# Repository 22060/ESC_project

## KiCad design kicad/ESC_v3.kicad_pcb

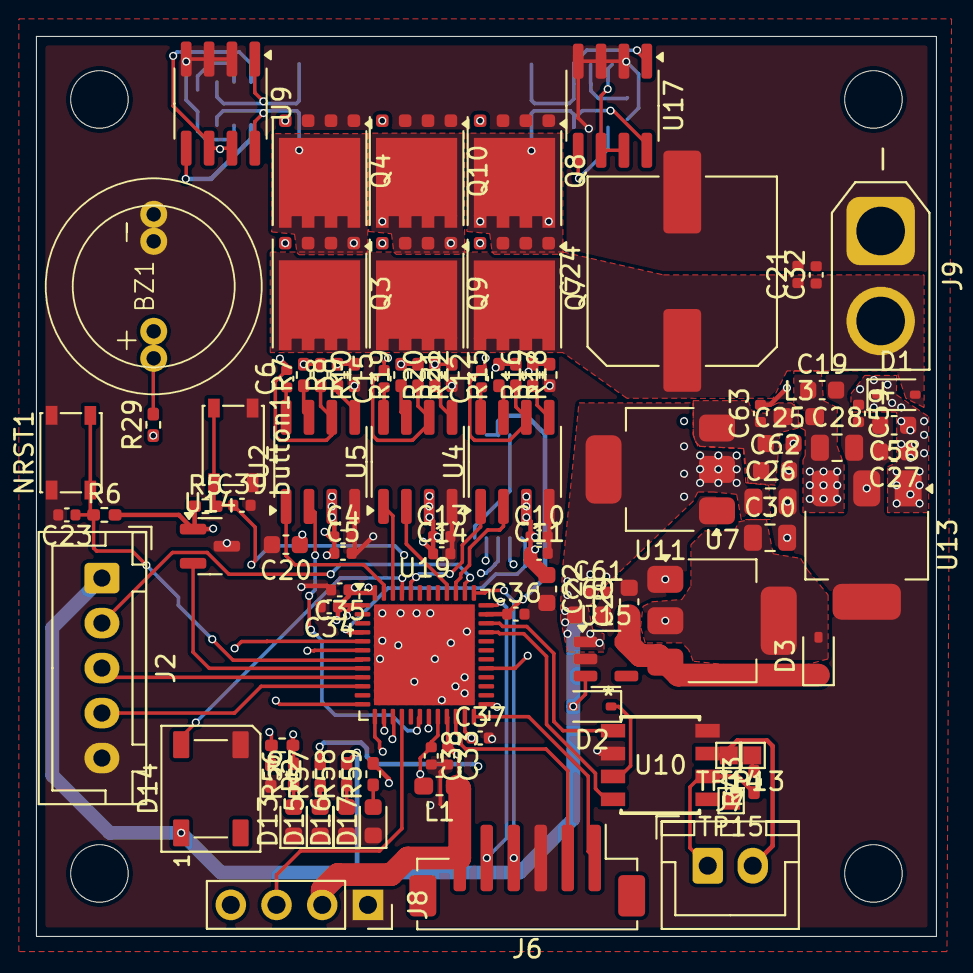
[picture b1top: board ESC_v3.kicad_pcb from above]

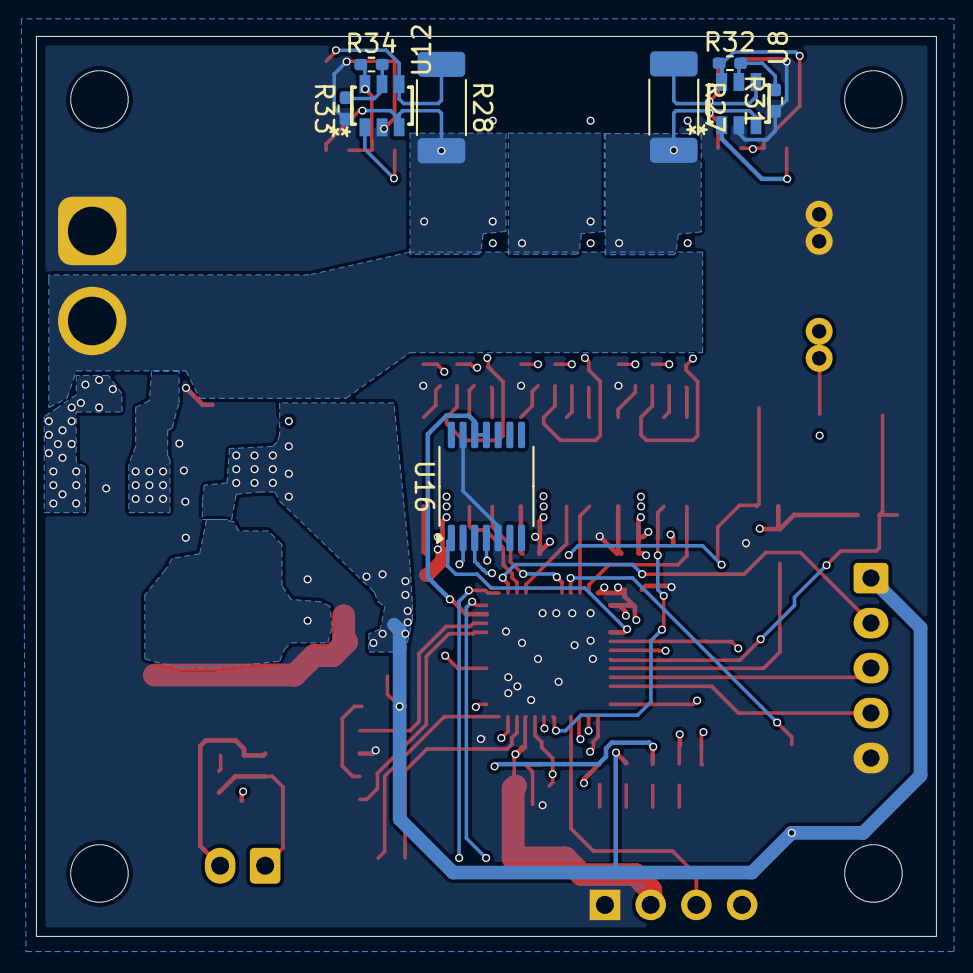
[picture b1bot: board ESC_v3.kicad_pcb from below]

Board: 6 copper layers, 50.0 x 50.0 mm, 109 parts (9 on the bottom side), 69 nets.

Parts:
BZ1: Buzzer; buzzer_unified
C4, C6, C10, C12, C13, C15, C23, C32, C38, C39, C59, C61, C63: 0.1u; C_0402_1005Metric
C5, C11, C14, C21, C33, C34, C35, C36, C37: 1u; C_0402_1005Metric
C19, C20, C22: 10u; C_0603_1608Metric
C24: 470u; C_Elec_10x10.2
C25, C29: 10uF; C_0603_1608Metric
C26, C28, C30: 22uF; C_0805_2012Metric
C27: 0.47uF; C_0603_1608Metric
C58, C60, C62: 100u; C_0603_1608Metric
D1, D2, D3: 1N5819WS; D_SOD-323
D13, D15, D16, D17: LED; LED_0603_1608Metric
D14: WS2812B; LED_WS2812B_PLCC4_5.0x5.0mm_P3.2mm
H1, H2, H3, H4: MountingHole; MountingHole_3.2mm_M3
J2: Conn_01x05_Pin; JST_XH_B5B-XH-A_1x05_P2.50mm_Vertical
J6: Conn_01x06_Pin; JST_ZH_B6B-ZR-SM4-TF_1x06-1MP_P1.50mm_Vertical
J7: Conn_01x02_Pin; JST_XH_B2B-XH-A_1x02_P2.50mm_Vertical
J8: Conn_01x04_Pin; PinSocket_1x04_P2.54mm_Vertical
J9: Conn_01x02_Pin; AMASS_XT30U-M_1x02_P5.0mm_Vertical
L1, L3: L; L_0603_1608Metric_Pad1.05x0.95mm_HandSolder
NRST1: SW_Push; SW_SPST_PTS810
Q3, Q4, Q7, Q8, Q9, Q10: RH6L040BGTB1; VSONP-8-1EP_5x6_P1.27mm
R1: 68k; R_0402_1005Metric_Pad0.72x0.64mm_HandSolder
R2, R5, R6, R9, R10, R17, R18, R21, R22, R57: 10k; R_0402_1005Metric_Pad0.72x0.64mm_HandSolder
R7, R8, R15, R16, R19, R20: 22; R_0402_1005Metric_Pad0.72x0.64mm_HandSolder
R27, R28: 2mΩ; R_2010_5025Metric_Pad1.40x2.65mm_HandSolder
R29: 100; R_0402_1005Metric_Pad0.72x0.64mm_HandSolder
R31, R32, R33, R34: 100k; R_0402_1005Metric_Pad0.72x0.64mm_HandSolder
R43: 120; R_0402_1005Metric_Pad0.72x0.64mm_HandSolder
R56: 22k; R_0402_1005Metric_Pad0.72x0.64mm_HandSolder
R58: 4.7k; R_0402_1005Metric_Pad0.72x0.64mm_HandSolder
R59: 2.2k; R_0402_1005Metric_Pad0.72x0.64mm_HandSolder
TP13, TP14, TP15: TestPoint; TestPoint_Pad_1.0x1.0mm
U2, U4, U5: L6387; SOIC-8_3.9x4.9mm_P1.27mm
U7: AMS1117-3.3; SOT-223-3_TabPin2
U8, U12: BD14210G; SSOP6
U9, U17: INA240A1D; SOIC-8_3.9x4.9mm_P1.27mm
U10: BD4104; SOP-J8
U11: AMS1117-5.0; SOT-223-3_TabPin2
U13: LM2937xMP; SOT-223-3_TabPin2
U14: MCP9700x-ETT; SOT-23
U15: MAX40200AUK; SOT-23-5
U16: AS5048A; TSSOP-14_4.4x5mm_P0.65mm
U19: STM32G431CBUx; QFN-48-1EP_7x7mm_P0.5mm_EP5.6x5.6mm
button1: SW_Push; SW_SPST_PTS810

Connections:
+3.3V: C30.1, C33.1, C34.1, C35.1, C36.1, C37.1, D3.2 (A), J6.6, J8.2, L1.1, R5.1, R6.2, R59.2, TP15.1, U7.2 (VO), U14.1 (V_{DD}), U16.11 (VDD5V), U16.12 (VDD3V), U19.1 (VBAT), U19.21 (VDDA), U19.23 (VDD), U19.35 (VDD), U19.48 (VDD)
+5V: C26.1, C60.1, C61.1, D2.2 (A), D14.1 (VDD), J2.1, R58.2, U11.2 (VO), U15.1 (VDD), U15.3 (EN)
+12V: C4.1, C5.1, C10.1, C11.1, C13.1, C14.1, C19.1, C20.1, C22.1, C28.1, L3.2, R57.2, U2.3 (VCC), U4.3 (VCC), U5.3 (VCC), U13.3 (VO)
/POWER/halfHbridge5/out1: C6.2, Q3.1 (S), Q4.3 (D), R10.2, R27.2, U2.6 (VS), U8.3 (VINP), U9.8 (+)
/POWER/halfHbridge7/out1: C12.2, Q7.1 (S), Q8.3 (D), R18.2, R28.2, U4.6 (VS), U12.3 (VINP), U17.8 (+)
/POWER/halfHbridge8/out1: C15.2, Q9.1 (S), Q10.3 (D), R22.2, U5.6 (VS)
ADC1_IN1: U14.2 (V_{OUT}), U19.8 (PA0)
ADC1_IN11: U12.1 (OUT), U17.5, U19.25 (PB12)
ADC2_IN10: R1.2, R2.1, U19.6 (PF1)
ADC2_IN12: U8.1 (OUT), U9.5, U19.19 (PB2)
CAN_H: J7.2, TP14.1, U10.7 (H)
CAN_L: J7.1, R43.1, U10.6 (L)
CAN_RX: U10.4 (RX), U19.33 (PA11)
CAN_TX: U10.1 (TX), U19.34 (PA12)
CLK: J6.4, U19.37 (PA14)
DAC1_OUT: R29.1, U19.12 (PA4)
DIO: J6.5, U19.36 (PA13)
GND: BZ1.2 (-), C4.2, C5.2, C10.2, C11.2, C13.2, C14.2, C19.2, C20.2, C21.2, C22.2, C23.2, C24.2, C25.2, C26.2, C27.2, C28.2, C29.2, C30.2, C32.2, C33.2, C34.2, C35.2, C36.2, C37.2, C38.2, C39.2, C58.2, C59.2, C60.2, C61.2, C62.2, C63.2, D13.1 (K), D14.3 (VSS), D15.1 (K), D16.1 (K), D17.1 (K), J2.5, J6.3, J8.1, J9.1, NRST1.1, Q4.1 (S), Q8.1 (S), Q10.1 (S), R2.2, R9.1, R17.1, R21.1, R31.1, R33.1, U2.4 (COM), U4.4 (COM), U5.4 (COM), U7.1 (GND), U8.2 (GND), U9.2 (GND), U9.3 (REF2), U9.4 (GND), U10.2 (GND), U10.8 (STB), U11.1 (GND), U12.2 (GND), U13.2 (GND), U14.3 (GND), U15.2 (GND), U16.5 (TEST), U16.13 (GND), U17.2 (GND), U17.3 (REF2), U17.4 (GND), U19.49 (VSS), button1.1
I2C_SCL: J8.3, U19.16 (PC4)
I2C_SDA: J8.4, U19.5 (PF0)
NRST: C23.1, NRST1.2, R6.1, U19.7 (PG10)
unnamed: BZ1.1 (+), R29.2
unnamed: C27.1, C58.1, C59.1, D1.1 (K), U13.1 (VI)
unnamed: D2.1 (K), U10.3 (VCC)
unnamed: C29.1, D3.1 (K), U7.3 (VI), U15.5 (OUT)
unnamed: D13.2 (A), R56.1
unnamed: D15.2 (A), R57.1
unnamed: D16.2 (A), R58.1
unnamed: D17.2 (A), R59.1
unnamed: Q3.2 (G), R7.2, R10.1
unnamed: Q4.2 (G), R8.2, R9.2
unnamed: Q7.2 (G), R15.2, R18.1
unnamed: Q8.2 (G), R16.2, R17.2
unnamed: Q9.2 (G), R19.2, R22.1
unnamed: Q10.2 (G), R20.2, R21.2
unnamed: R43.2, TP13.1
unnamed: R7.1, U2.7 (HO)
unnamed: R8.1, U2.5 (LO)
unnamed: C6.1, U2.8 (VB)
unnamed: R15.1, U4.7 (HO)
unnamed: R16.1, U4.5 (LO)
unnamed: C12.1, U4.8 (VB)
unnamed: R19.1, U5.7 (HO)
unnamed: R20.1, U5.5 (LO)
unnamed: C15.1, U5.8 (VB)
unnamed: R31.2, R32.2, U8.5 (REF)
unnamed: R27.1, U8.4 (VINM), U9.1 (-)
unnamed: C25.1, C62.1, C63.1, L3.1, U11.3 (VI)
unnamed: R33.2, R34.2, U12.5 (REF)
unnamed: R28.1, U12.4 (VINM), U17.1 (-)
RX: J6.1, U19.24 (PB11)
SPI1_MISO: U16.3 (MISO), U19.14 (PA6)
SPI1_MOSI: U16.4 (MOSI), U19.15 (PA7)
SPI1_SCK: U16.2 (CLK), U19.13 (PA5)
SS: U16.1 (~CSn), U19.4 (PC15)
TIM2_CH1: J2.2, U19.38 (PA15)
TIM2_CH2: J2.3, U19.9 (PA1)
TIM2_CH3: J2.4, U19.10 (PA2)
TIM4_CH2: D14.4 (DIN), U19.45 (PB7)
TIM8_CH1: U4.1 (HIN), U19.44 (PB6)
TIM8_CH1N: U4.2 (LIN), U19.39 (PC10)
TIM8_CH2: U5.1 (HIN), U19.46 (PB8)
TIM8_CH2N: U5.2 (LIN), U19.40 (PC11)
TIM8_CH3: U2.1 (HIN), U19.47 (PB9)
TIM8_CH3N: U2.2 (LIN), U19.18 (PB1)
TX: J6.2, U19.22 (PB10)
VCC: C21.1, C24.1, C32.1, D1.2 (A), J9.2, Q3.3 (D), Q7.3 (D), Q9.3 (D), R1.1, R56.2
VREF: C38.1, L1.2, R32.1, R34.1, U8.6 (VDD), U9.6 (V+), U9.7 (REF1), U12.6 (VDD), U17.6 (V+), U17.7 (REF1), U19.20 (VREF+)
button: C39.1, R5.2, U19.29 (PC6), button1.2

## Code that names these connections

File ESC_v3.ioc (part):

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Mcu.Name=STM32G431C(6-8-B)Ux
Mcu.Package=UFQFPN48
Mcu.UserName=STM32G431CBUx
PA0.Mode=IN1-Single-Ended
PA0.Signal=ADC1_IN1
PA1.Signal=S_TIM2_CH2
PA10.Signal=S_TIM1_CH3
PA11.Mode=FDCAN_Activate
PA11.Signal=FDCAN1_RX
PA12.Mode=FDCAN_Activate
PA12.Signal=FDCAN1_TX
PA13.Mode=Serial_Wire
PA13.Signal=SYS_JTMS-SWDIO
PA14.Mode=Serial_Wire
PA14.Signal=SYS_JTCK-SWCLK
PA15.Signal=S_TIM2_CH1
PA2.Signal=SharedStack_PA2
PA2.Stacked=true
PA3.Mode=PGA_Internally_Connected
PA3.Signal=OPAMP1_VINP
PA4.Signal=COMP_DAC11_group
PA5.Mode=Full_Duplex_Master
PA5.Signal=SPI1_SCK
PA6.Mode=Full_Duplex_Master
PA6.Signal=SPI1_MISO
PA7.Mode=Full_Duplex_Master
PA7.Signal=SPI1_MOSI
PA8.Signal=S_TIM1_CH1
PA9.Signal=S_TIM1_CH2
PB0.Mode=PGA_Internally_Connected
PB0.Signal=OPAMP2_VINP
PB1.Mode=PWM Generation3 CH3 CH3N
PB1.Signal=TIM8_CH3N
PB10.Mode=Asynchronous
PB10.Signal=USART3_TX
PB11.Mode=Asynchronous
PB11.Signal=USART3_RX
PB12.Mode=IN11-Single-Ended
PB12.Signal=ADC1_IN11
PB13.Mode=PGA_Internally_Connected
PB13.Signal=OPAMP3_VINP
PB14.Mode=PWM Generation2 CH2 CH2N
PB14.Signal=TIM1_CH2N
PB15.Mode=PWM Generation3 CH3 CH3N
PB15.Signal=TIM1_CH3N
PB2.Mode=IN12-Single-Ended
PB2.Signal=ADC2_IN12
PB3.Signal=SharedStack_PB3
PB3.Stacked=true
PB4.Signal=SharedStack_PB4
PB4.Stacked=true
PB5.Signal=S_TIM3_CH2
PB5.Stacked=true
PB6.Signal=S_TIM8_CH1
PB7.Signal=S_TIM4_CH2
PB8-BOOT0.Signal=S_TIM8_CH2
PB9.Signal=S_TIM8_CH3
PC10.Mode=PWM Generation1 CH1 CH1N
PC10.Signal=TIM8_CH1N
PC11.Mode=PWM Generation2 CH2 CH2N
PC11.Signal=TIM8_CH2N
PC13.Mode=PWM Generation1 CH1 CH1N
PC13.Signal=TIM1_CH1N
PC14-OSC32_IN.Signal=GPIO_Input
PC15-OSC32_OUT.Signal=GPIO_Output
PC4.Mode=I2C
PC4.Signal=I2C2_SCL
PC6.Signal=GPIO_Input
PF0-OSC_IN.Mode=I2C
PF0-OSC_IN.Signal=I2C2_SDA
PF1-OSC_OUT.Mode=IN10-Single-Ended
PF1-OSC_OUT.Signal=ADC2_IN10
RCC.HSE_VALUE=8000000
RCC.SYSCLKFreq_VALUE=100000000
RCC.SYSCLKSource=RCC_SYSCLKSOURCE_PLLCLK
board=custom

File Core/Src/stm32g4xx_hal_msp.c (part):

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    __HAL_RCC_GPIOA_CLK_ENABLE();
    __HAL_RCC_GPIOB_CLK_ENABLE();
    /**ADC1 GPIO Configuration
    PA0     ------> ADC1_IN1
    PB12     ------> ADC1_IN11
    */
    GPIO_InitStruct.Pin = GPIO_PIN_0;
    GPIO_InitStruct.Mode = GPIO_MODE_ANALOG;
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    __HAL_RCC_GPIOF_CLK_ENABLE();
    __HAL_RCC_GPIOB_CLK_ENABLE();
    /**ADC2 GPIO Configuration
    PF1-OSC_OUT     ------> ADC2_IN10
    PB2     ------> ADC2_IN12
    */
    GPIO_InitStruct.Pin = GPIO_PIN_1;
    GPIO_InitStruct.Mode = GPIO_MODE_ANALOG;
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    }

    /**ADC1 GPIO Configuration
    PA0     ------> ADC1_IN1
    PB12     ------> ADC1_IN11
    */
    HAL_GPIO_DeInit(GPIOA, GPIO_PIN_0);

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    }

    /**ADC2 GPIO Configuration
    PF1-OSC_OUT     ------> ADC2_IN10
    PB2     ------> ADC2_IN12
    */
    HAL_GPIO_DeInit(GPIOF, GPIO_PIN_1);

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
    __HAL_RCC_GPIOA_CLK_ENABLE();
    /**DAC1 GPIO Configuration
    PA4     ------> DAC1_OUT1
    */
    GPIO_InitStruct.Pin = GPIO_PIN_4;
    GPIO_InitStruct.Mode = GPIO_MODE_ANALOG;
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    __HAL_RCC_DAC1_CLK_DISABLE();

    /**DAC1 GPIO Configuration
    PA4     ------> DAC1_OUT1
    */
    HAL_GPIO_DeInit(GPIOA, GPIO_PIN_4);

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
    __HAL_RCC_GPIOA_CLK_ENABLE();
    /**FDCAN1 GPIO Configuration
    PA11     ------> FDCAN1_RX
    PA12     ------> FDCAN1_TX
    */
    GPIO_InitStruct.Pin = GPIO_PIN_11|GPIO_PIN_12;
    GPIO_InitStruct.Mode = GPIO_MODE_AF_PP;
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    __HAL_RCC_FDCAN_CLK_DISABLE();

    /**FDCAN1 GPIO Configuration
    PA11     ------> FDCAN1_RX
    PA12     ------> FDCAN1_TX
    */
    HAL_GPIO_DeInit(GPIOA, GPIO_PIN_11|GPIO_PIN_12);

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    __HAL_RCC_GPIOF_CLK_ENABLE();
    __HAL_RCC_GPIOC_CLK_ENABLE();
    /**I2C2 GPIO Configuration
    PF0-OSC_IN     ------> I2C2_SDA
    PC4     ------> I2C2_SCL
    */
    GPIO_InitStruct.Pin = GPIO_PIN_0;
    GPIO_InitStruct.Mode = GPIO_MODE_AF_OD;
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    __HAL_RCC_I2C2_CLK_DISABLE();

    /**I2C2 GPIO Configuration
    PF0-OSC_IN     ------> I2C2_SDA
    PC4     ------> I2C2_SCL
    */
    HAL_GPIO_DeInit(GPIOF, GPIO_PIN_0);

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
    __HAL_RCC_GPIOA_CLK_ENABLE();
    /**SPI1 GPIO Configuration
    PA5     ------> SPI1_SCK
    PA6     ------> SPI1_MISO
    PA7     ------> SPI1_MOSI
    */
    GPIO_InitStruct.Pin = GPIO_PIN_5|GPIO_PIN_6|GPIO_PIN_7;
    GPIO_InitStruct.Mode = GPIO_MODE_AF_PP;
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    __HAL_RCC_SPI1_CLK_DISABLE();

    /**SPI1 GPIO Configuration
    PA5     ------> SPI1_SCK
    PA6     ------> SPI1_MISO
    PA7     ------> SPI1_MOSI
    */
    HAL_GPIO_DeInit(GPIOA, GPIO_PIN_5|GPIO_PIN_6|GPIO_PIN_7);

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
    __HAL_RCC_GPIOA_CLK_ENABLE();
    /**TIM2 GPIO Configuration
    PA1     ------> TIM2_CH2
    PA15     ------> TIM2_CH1
    */
    GPIO_InitStruct.Pin = GPIO_PIN_1|GPIO_PIN_15;
    GPIO_InitStruct.Mode = GPIO_MODE_AF_PP;
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
    __HAL_RCC_GPIOB_CLK_ENABLE();
    /**TIM4 GPIO Configuration
    PB7     ------> TIM4_CH2
    */
    GPIO_InitStruct.Pin = GPIO_PIN_7;
    GPIO_InitStruct.Mode = GPIO_MODE_AF_PP;
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    __HAL_RCC_GPIOB_CLK_ENABLE();
    __HAL_RCC_GPIOC_CLK_ENABLE();
    /**TIM8 GPIO Configuration
    PB1     ------> TIM8_CH3N
    PC10     ------> TIM8_CH1N
    PC11     ------> TIM8_CH2N
    PB6     ------> TIM8_CH1
    PB8-BOOT0     ------> TIM8_CH2
    PB9     ------> TIM8_CH3
    */
    GPIO_InitStruct.Pin = GPIO_PIN_1;
    GPIO_InitStruct.Mode = GPIO_MODE_AF_PP;
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    __HAL_RCC_TIM2_CLK_DISABLE();

    /**TIM2 GPIO Configuration
    PA1     ------> TIM2_CH2
    PA15     ------> TIM2_CH1
    */
    HAL_GPIO_DeInit(GPIOA, GPIO_PIN_1|GPIO_PIN_15);

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
    __HAL_RCC_GPIOB_CLK_ENABLE();
    /**USART3 GPIO Configuration
    PB10     ------> USART3_TX
    PB11     ------> USART3_RX
    */
    GPIO_InitStruct.Pin = GPIO_PIN_10|GPIO_PIN_11;
    GPIO_InitStruct.Mode = GPIO_MODE_AF_PP;
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    __HAL_RCC_USART3_CLK_DISABLE();

    /**USART3 GPIO Configuration
    PB10     ------> USART3_TX
    PB11     ------> USART3_RX
    */
    HAL_GPIO_DeInit(GPIOB, GPIO_PIN_10|GPIO_PIN_11);

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
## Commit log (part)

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2026-05-16 ESC_v3 final version
2026-05-16 fix file name
2026-06-11 test
2026-06-12 circuit finish
2026-06-15 final
2026-06-17 add .ioc to v2_mini branch and setting STM32G431VBx3 for STSPIN32G4
2026-06-21 finish
2026-06-23 order finished
2026-06-26 add v2_mini_mini
2026-06-29 dlt .lck
2026-06-29 コード大体終わり．あとは3Dプリンターで出力して動作チェック

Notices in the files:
Core/Src/stm32g4xx_hal_msp.c:
Copyright (c) 2026 STMicroelectronics.
All rights reserved.
This software is licensed under terms that can be found in the LICENSE file
